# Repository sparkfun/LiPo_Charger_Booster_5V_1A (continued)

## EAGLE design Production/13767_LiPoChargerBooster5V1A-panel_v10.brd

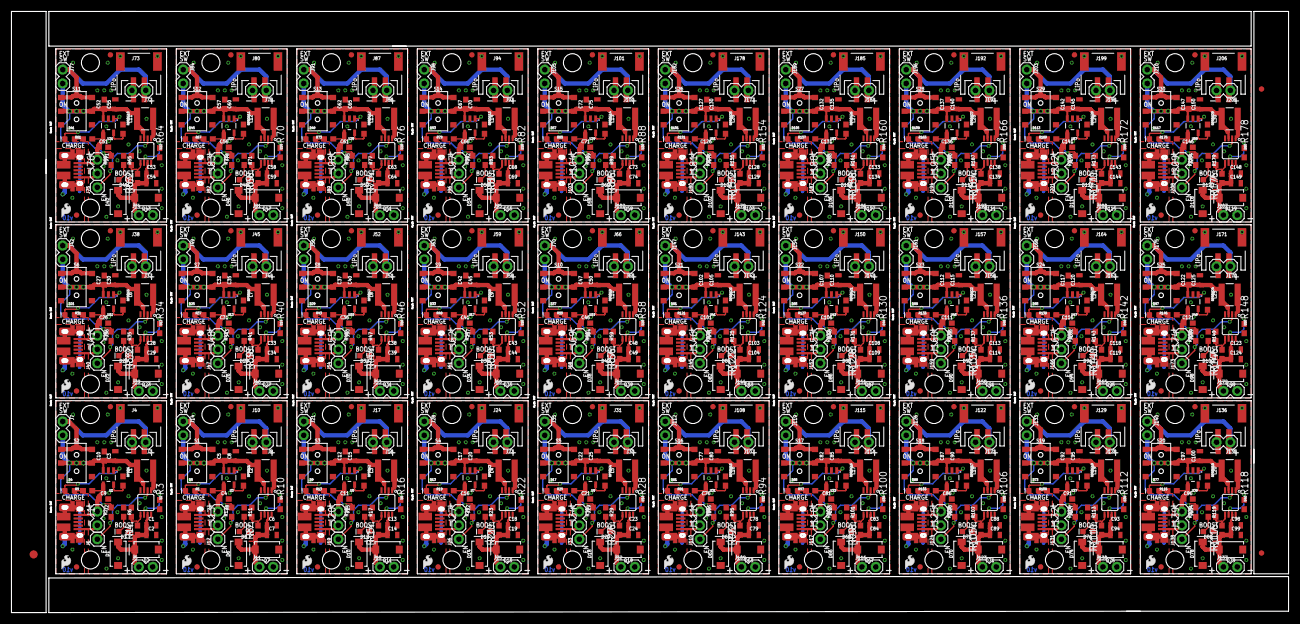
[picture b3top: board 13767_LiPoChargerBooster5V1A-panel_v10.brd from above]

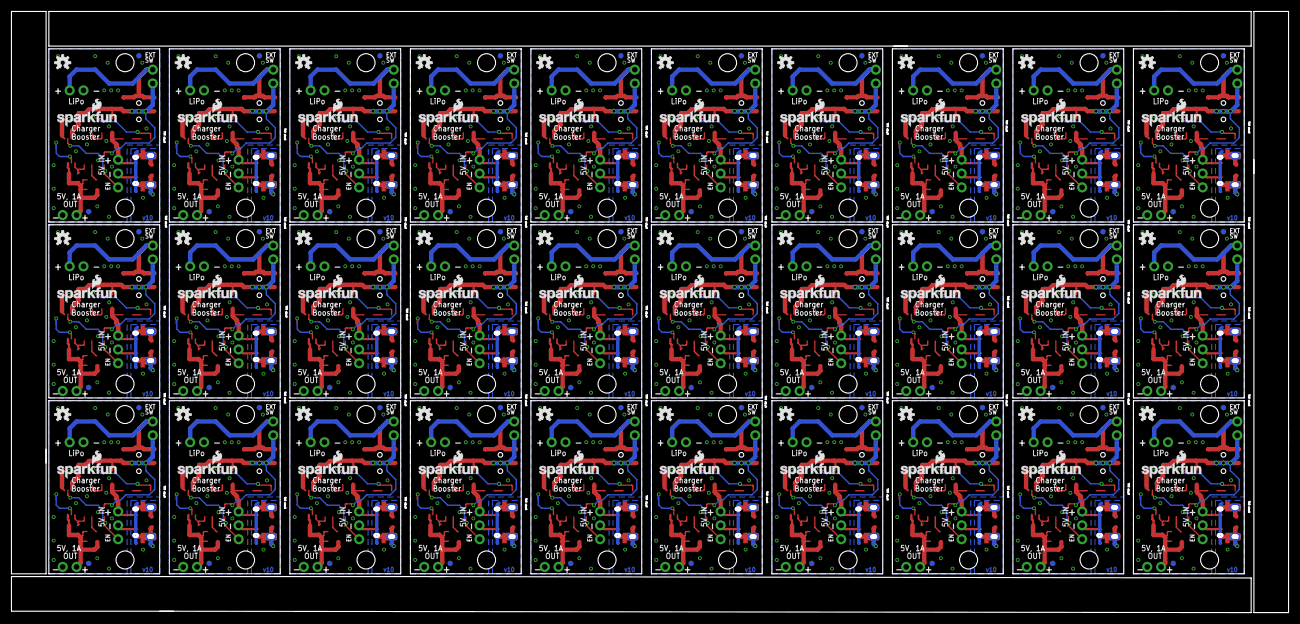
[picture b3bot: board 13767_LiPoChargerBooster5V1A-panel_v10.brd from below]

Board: 2 copper layers, 234.2 x 110.2 mm, 1113 parts (150 on the bottom side), 420 nets.

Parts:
C1, C2, C3, C6, C7, C8, C13, C14, C15, C18, C19, C20, C23, C24, C25, C28, C29, C30, C33, C34, C35, C38, C39, C40, C43, C44, C45, C48, C49, C50, C53, C54, C55, C58, C59, C60, C63, C64, C65, C68, C69, C70, C73, C74, C75, C78, C79, C80, C83, C84, C85, C88, C89, C90, C93, C94, C95, C98, C99, C100, C103, C104, C105, C108, C109, C110, C113, C114, C115, C118, C119, C120, C123, C124, C125, C128, C129, C130, C133, C134, C135, C138, C139, C140, C143, C144, C145, C148, C149, C150: 22uF; 0805
C4, C5, C9, C10, C11, C12, C16, C17, C21, C22, C26, C27, C31, C32, C36, C37, C41, C42, C46, C47, C51, C52, C56, C57, C61, C62, C66, C67, C71, C72, C76, C77, C81, C82, C86, C87, C91, C92, C96, C97, C101, C102, C106, C107, C111, C112, C116, C117, C121, C122, C126, C127, C131, C132, C136, C137, C141, C142, C146, C147: 4.7uF; 0603
D1, D2, D6, D7, D10, D11, D14, D15, D18, D19, D22, D23, D26, D27, D30, D31, D34, D35, D38, D39, D42, D43, D46, D47, D50, D51, D54, D55, D58, D59, D62, D63, D66, D67, D70, D71, D74, D75, D78, D79, D82, D83, D86, D87, D90, D91, D94, D95, D98, D99, D102, D103, D106, D107, D110, D111, D114, D115, D118, D119: 3A/40V/500mV; SMA-DIODE
D3, D8, D12, D16, D20, D24, D28, D32, D36, D40, D44, D48, D52, D56, D60, D64, D68, D72, D76, D80, D84, D88, D92, D96, D100, D104, D108, D112, D116, D120: RED; LED-0603
D4, D5, D9, D13, D17, D21, D25, D29, D33, D37, D41, D45, D49, D53, D57, D61, D65, D69, D73, D77, D81, D85, D89, D93, D97, D101, D105, D109, D113, D117: BLUE; LED-0603
E$1: FIDUCIAL-1.5X3
E$5, E$6: FIDUCIAL-1X2
J1, J13, J20, J27, J34, J41, J48, J55, J62, J69, J76, J83, J90, J97, J104, J111, J118, J125, J132, J139, J146, J153, J160, J167, J174, J181, J188, J195, J202, J209: AMP FCI 10103594-0001LF; USB-MICROB-PTH
J2, J3, J7, J8, J9, J14, J15, J16, J21, J22, J23, J28, J29, J30, J35, J36, J37, J42, J43, J44, J49, J50, J51, J56, J57, J58, J63, J64, J65, J70, J71, J72, J77, J78, J79, J84, J85, J86, J91, J92, J93, J98, J99, J100, J105, J106, J107, J112, J113, J114, J119, J120, J121, J126, J127, J128, J133, J134, J135, J140, J141, J142, J147, J148, J149, J154, J155, J156, J161, J162, J163, J168, J169, J170, J175, J176, J177, J182, J183, J184, J189, J190, J191, J196, J197, J198, J203, J204, J205, J210: PTH; 1X02
J4, J10, J17, J24, J31, J38, J45, J52, J59, J66, J73, J80, J87, J94, J101, J108, J115, J122, J129, J136, J143, J150, J157, J164, J171, J178, J185, J192, J199, J206: JST; JST-2-SMD
J5, J11, J18, J25, J32, J39, J46, J53, J60, J67, J74, J81, J88, J95, J102, J109, J116, J123, J130, J137, J144, J151, J158, J165, J172, J179, J186, J193, J200, J207: 1X02
J6, J12, J19, J26, J33, J40, J47, J54, J61, J68, J75, J82, J89, J96, J103, J110, J117, J124, J131, J138, J145, J152, J159, J166, J173, J180, J187, J194, J201, J208: 1X01
JP1, JP2, JP4, JP10, JP11, JP12, JP13, JP16, JP18, JP19, JP20, JP21, JP25, JP26, JP27, JP28, JP32, JP33, JP34, JP35, JP39, JP40, JP41, JP42, JP46, JP47, JP48, JP49, JP53, JP54, JP55, JP56, JP60, JP61, JP62, JP63, JP67, JP68, JP69, JP70, JP74, JP75, JP76, JP77, JP81, JP82, JP83, JP84, JP88, JP89, JP90, JP91, JP95, JP96, JP97, JP98, JP102, JP103, JP104, JP105, JP109, JP110, JP111, JP112, JP116, JP117, JP118, JP119, JP123, JP124, JP125, JP126, JP130, JP131, JP132, JP133, JP137, JP138, JP139, JP140, JP144, JP145, JP146, JP147, JP151, JP152, JP153, JP154, JP158, JP159, JP160, JP161, JP165, JP166, JP167, JP168, JP172, JP173, JP174, JP175, JP179, JP180, JP181, JP182, JP186, JP187, JP188, JP189, JP193, JP194, JP195, JP196, JP200, JP201, JP202, JP203, JP207, JP208, JP209, JP210: FIDUCIAL1X2; FIDUCIAL-1X2
JP3, JP5, JP14, JP22, JP29, JP36, JP43, JP50, JP57, JP64, JP71, JP78, JP85, JP92, JP99, JP106, JP113, JP120, JP127, JP134, JP141, JP148, JP155, JP162, JP169, JP176, JP183, JP190, JP197, JP204: SFE_LOGO_NAME_FLAME.1_INCH; SFE_LOGO_NAME_FLAME_.1
JP6, JP7, JP8, JP9, JP15, JP17, JP23, JP24, JP30, JP31, JP37, JP38, JP44, JP45, JP51, JP52, JP58, JP59, JP65, JP66, JP72, JP73, JP79, JP80, JP86, JP87, JP93, JP94, JP100, JP101, JP107, JP108, JP114, JP115, JP121, JP122, JP128, JP129, JP135, JP136, JP142, JP143, JP149, JP150, JP156, JP157, JP163, JP164, JP170, JP171, JP177, JP178, JP184, JP185, JP191, JP192, JP198, JP199, JP205, JP206: STAND-OFF
L1, L2, L3, L4, L5, L6, L7, L8, L9, L10, L11, L12, L13, L14, L15, L16, L17, L18, L19, L20, L21, L22, L23, L24, L25, L26, L27, L28, L29, L30: 2.2UH3A; INDUCTOR_4X4MM
LOGO1, LOGO2, LOGO3, LOGO4, LOGO5, LOGO6, LOGO7, LOGO8, LOGO9, LOGO10, LOGO11, LOGO12, LOGO13, LOGO14, LOGO15, LOGO16, LOGO17, LOGO18, LOGO19, LOGO20, LOGO21, LOGO22, LOGO23, LOGO24, LOGO25, LOGO26, LOGO27, LOGO28, LOGO29, LOGO30: SFE_LOGO_FLAME.1_INCH; SFE_LOGO_FLAME_.1
R1, R8, R15, R21, R27, R33, R39, R45, R51, R57, R63, R69, R75, R81, R87, R93, R99, R105, R111, R117, R123, R129, R135, R141, R147, R153, R159, R165, R171, R177: 100k; 0603
R2, R12, R18, R24, R30, R36, R42, R48, R54, R60, R66, R72, R78, R84, R90, R96, R102, R108, R114, R120, R126, R132, R138, R144, R150, R156, R162, R168, R174, R180: 10k; 0603
R3, R10, R16, R22, R28, R34, R40, R46, R52, R58, R64, R70, R76, R82, R88, R94, R100, R106, R112, R118, R124, R130, R136, R142, R148, R154, R160, R166, R172, R178: DNP; 0603
R4, R7, R14, R20, R26, R32, R38, R44, R50, R56, R62, R68, R74, R80, R86, R92, R98, R104, R110, R116, R122, R128, R134, R140, R146, R152, R158, R164, R170, R176: 750K; 0603
R5, R9, R13, R19, R25, R31, R37, R43, R49, R55, R61, R67, R73, R79, R85, R91, R97, R103, R109, R115, R121, R127, R133, R139, R145, R151, R157, R163, R169, R175: 1k; 0603
R6, R11, R17, R23, R29, R35, R41, R47, R53, R59, R65, R71, R77, R83, R89, R95, R101, R107, R113, R119, R125, R131, R137, R143, R149, R155, R161, R167, R173, R179: 4.7k; 0603
RPROG, RPROG1, RPROG2, RPROG3, RPROG4, RPROG5, RPROG6, RPROG7, RPROG8, RPROG9, RPROG10, RPROG11, RPROG12, RPROG13, RPROG14, RPROG15, RPROG16, RPROG17, RPROG18, RPROG19, RPROG20, RPROG21, RPROG22, RPROG23, RPROG24, RPROG25, RPROG26, RPROG27, RPROG28, RPROG29: 2.0k; 0603
S1, S2, S3, S4, S5, S6, S7, S8, S9, S10, S11, S12, S13, S14, S15, S16, S17, S18, S19, S20, S21, S22, S23, S24, S25, S26, S27, S28, S29, S30: SWITCH_DPDT_SMD_AYZ0202
TP1, TP2, TP3, TP4, TP5, TP6, TP7, TP8, TP9, TP10, TP11, TP12, TP13, TP14, TP15, TP16, TP17, TP18, TP19, TP20, TP21, TP22, TP23, TP24, TP25, TP26, TP27, TP28, TP29, TP30: TEST-POINT3; PAD.03X.03
U1, U3, U5, U7, U9, U11, U13, U15, U17, U19, U21, U23, U25, U27, U29, U31, U33, U35, U37, U39, U41, U43, U45, U47, U49, U51, U53, U55, U57, U59: MCP73831; SOT23-5
U2, U4, U6, U8, U10, U12, U14, U16, U18, U20, U22, U24, U26, U28, U30, U32, U34, U36, U38, U40, U42, U44, U46, U48, U50, U52, U54, U56, U58, U60: PAM2401; MSOP8
U$1, U$2, U$3, U$4, U$5, U$6, U$7, U$8, U$9, U$10, U$11, U$12, U$13, U$14, U$15, U$16, U$17, U$18, U$19, U$20, U$21, U$22, U$23, U$24, U$25, U$26, U$27, U$28, U$29, U$30: OSHW-LOGOS; OSHW-LOGO-S

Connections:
5VIN: C9.1, J1.VBUS, J2.1, R9.2, U1.4
5VIN1: C4.1, J8.1, J13.VBUS, R5.2, U3.4
5VIN2: C11.1, J15.1, J20.VBUS, R13.2, U5.4
5VIN3: C16.1, J22.1, J27.VBUS, R19.2, U7.4
5VIN4: C21.1, J29.1, J34.VBUS, R25.2, U9.4
5VIN5: C26.1, J36.1, J41.VBUS, R31.2, U11.4
5VIN6: C31.1, J43.1, J48.VBUS, R37.2, U13.4
5VIN7: C36.1, J50.1, J55.VBUS, R43.2, U15.4
5VIN8: C41.1, J57.1, J62.VBUS, R49.2, U17.4
5VIN9: C46.1, J64.1, J69.VBUS, R55.2, U19.4
5VIN10: C51.1, J71.1, J76.VBUS, R61.2, U21.4
5VIN11: C56.1, J78.1, J83.VBUS, R67.2, U23.4
5VIN12: C61.1, J85.1, J90.VBUS, R73.2, U25.4
5VIN13: C66.1, J92.1, J97.VBUS, R79.2, U27.4
5VIN14: C71.1, J99.1, J104.VBUS, R85.2, U29.4
5VIN15: C76.1, J106.1, J111.VBUS, R91.2, U31.4
5VIN16: C81.1, J113.1, J118.VBUS, R97.2, U33.4
5VIN17: C86.1, J120.1, J125.VBUS, R103.2, U35.4
5VIN18: C91.1, J127.1, J132.VBUS, R109.2, U37.4
5VIN19: C96.1, J134.1, J139.VBUS, R115.2, U39.4
5VIN20: C101.1, J141.1, J146.VBUS, R121.2, U41.4
5VIN21: C106.1, J148.1, J153.VBUS, R127.2, U43.4
5VIN22: C111.1, J155.1, J160.VBUS, R133.2, U45.4
5VIN23: C116.1, J162.1, J167.VBUS, R139.2, U47.4
5VIN24: C121.1, J169.1, J174.VBUS, R145.2, U49.4
5VIN25: C126.1, J176.1, J181.VBUS, R151.2, U51.4
5VIN26: C131.1, J183.1, J188.VBUS, R157.2, U53.4
5VIN27: C136.1, J190.1, J195.VBUS, R163.2, U55.4
5VIN28: C141.1, J197.1, J202.VBUS, R169.2, U57.4
5VIN29: C146.1, J204.1, J209.VBUS, R175.2, U59.4
EN: J6.1, R2.1, U2.2
EN1: J12.1, R12.1, U4.2
EN2: J19.1, R18.1, U6.2
EN3: J26.1, R24.1, U8.2
EN4: J33.1, R30.1, U10.2
EN5: J40.1, R36.1, U12.2
EN6: J47.1, R42.1, U14.2
EN7: J54.1, R48.1, U16.2
EN8: J61.1, R54.1, U18.2
EN9: J68.1, R60.1, U20.2
EN10: J75.1, R66.1, U22.2
EN11: J82.1, R72.1, U24.2
EN12: J89.1, R78.1, U26.2
EN13: J96.1, R84.1, U28.2
EN14: J103.1, R90.1, U30.2
EN15: J110.1, R96.1, U32.2
EN16: J117.1, R102.1, U34.2
EN17: J124.1, R108.1, U36.2
EN18: J131.1, R114.1, U38.2
EN19: J138.1, R120.1, U40.2
EN20: J145.1, R126.1, U42.2
EN21: J152.1, R132.1, U44.2
EN22: J159.1, R138.1, U46.2
EN23: J166.1, R144.1, U48.2
EN24: J173.1, R150.1, U50.2
EN25: J180.1, R156.1, U52.2
EN26: J187.1, R162.1, U54.2
EN27: J194.1, R168.1, U56.2
EN28: J201.1, R174.1, U58.2
EN29: J208.1, R180.1, U60.2
GND: C1.2, C2.2, C3.2, C9.2, C10.2, D1.A, D2.A, J1.GND, J2.2, J3.2, J4.1, J5.2, R1.1, R3.1, R6.1, RPROG.2, U1.2, U2.4, U2.8
GND1: C4.2, C5.2, C6.2, C7.2, C8.2, D6.A, D7.A, J8.2, J9.2, J10.1, J11.2, J13.GND, R8.1, R10.1, R11.1, RPROG1.2, U3.2, U4.4, U4.8
GND2: C11.2, C12.2, C13.2, C14.2, C15.2, D10.A, D11.A, J15.2, J16.2, J17.1, J18.2, J20.GND, R15.1, R16.1, R17.1, RPROG2.2, U5.2, U6.4, U6.8
GND3: C16.2, C17.2, C18.2, C19.2, C20.2, D14.A, D15.A, J22.2, J23.2, J24.1, J25.2, J27.GND, R21.1, R22.1, R23.1, RPROG3.2, U7.2, U8.4, U8.8
GND4: C21.2, C22.2, C23.2, C24.2, C25.2, D18.A, D19.A, J29.2, J30.2, J31.1, J32.2, J34.GND, R27.1, R28.1, R29.1, RPROG4.2, U9.2, U10.4, U10.8
GND5: C26.2, C27.2, C28.2, C29.2, C30.2, D22.A, D23.A, J36.2, J37.2, J38.1, J39.2, J41.GND, R33.1, R34.1, R35.1, RPROG5.2, U11.2, U12.4, U12.8
GND6: C31.2, C32.2, C33.2, C34.2, C35.2, D26.A, D27.A, J43.2, J44.2, J45.1, J46.2, J48.GND, R39.1, R40.1, R41.1, RPROG6.2, U13.2, U14.4, U14.8
GND7: C36.2, C37.2, C38.2, C39.2, C40.2, D30.A, D31.A, J50.2, J51.2, J52.1, J53.2, J55.GND, R45.1, R46.1, R47.1, RPROG7.2, U15.2, U16.4, U16.8
GND8: C41.2, C42.2, C43.2, C44.2, C45.2, D34.A, D35.A, J57.2, J58.2, J59.1, J60.2, J62.GND, R51.1, R52.1, R53.1, RPROG8.2, U17.2, U18.4, U18.8
GND9: C46.2, C47.2, C48.2, C49.2, C50.2, D38.A, D39.A, J64.2, J65.2, J66.1, J67.2, J69.GND, R57.1, R58.1, R59.1, RPROG9.2, U19.2, U20.4, U20.8
GND10: C51.2, C52.2, C53.2, C54.2, C55.2, D42.A, D43.A, J71.2, J72.2, J73.1, J74.2, J76.GND, R63.1, R64.1, R65.1, RPROG10.2, U21.2, U22.4, U22.8
GND11: C56.2, C57.2, C58.2, C59.2, C60.2, D46.A, D47.A, J78.2, J79.2, J80.1, J81.2, J83.GND, R69.1, R70.1, R71.1, RPROG11.2, U23.2, U24.4, U24.8
GND12: C61.2, C62.2, C63.2, C64.2, C65.2, D50.A, D51.A, J85.2, J86.2, J87.1, J88.2, J90.GND, R75.1, R76.1, R77.1, RPROG12.2, U25.2, U26.4, U26.8
GND13: C66.2, C67.2, C68.2, C69.2, C70.2, D54.A, D55.A, J92.2, J93.2, J94.1, J95.2, J97.GND, R81.1, R82.1, R83.1, RPROG13.2, U27.2, U28.4, U28.8
GND14: C71.2, C72.2, C73.2, C74.2, C75.2, D58.A, D59.A, J99.2, J100.2, J101.1, J102.2, J104.GND, R87.1, R88.1, R89.1, RPROG14.2, U29.2, U30.4, U30.8
GND15: C76.2, C77.2, C78.2, C79.2, C80.2, D62.A, D63.A, J106.2, J107.2, J108.1, J109.2, J111.GND, R93.1, R94.1, R95.1, RPROG15.2, U31.2, U32.4, U32.8
GND16: C81.2, C82.2, C83.2, C84.2, C85.2, D66.A, D67.A, J113.2, J114.2, J115.1, J116.2, J118.GND, R99.1, R100.1, R101.1, RPROG16.2, U33.2, U34.4, U34.8
GND17: C86.2, C87.2, C88.2, C89.2, C90.2, D70.A, D71.A, J120.2, J121.2, J122.1, J123.2, J125.GND, R105.1, R106.1, R107.1, RPROG17.2, U35.2, U36.4, U36.8
GND18: C91.2, C92.2, C93.2, C94.2, C95.2, D74.A, D75.A, J127.2, J128.2, J129.1, J130.2, J132.GND, R111.1, R112.1, R113.1, RPROG18.2, U37.2, U38.4, U38.8
GND19: C96.2, C97.2, C98.2, C99.2, C100.2, D78.A, D79.A, J134.2, J135.2, J136.1, J137.2, J139.GND, R117.1, R118.1, R119.1, RPROG19.2, U39.2, U40.4, U40.8
GND20: C101.2, C102.2, C103.2, C104.2, C105.2, D82.A, D83.A, J141.2, J142.2, J143.1, J144.2, J146.GND, R123.1, R124.1, R125.1, RPROG20.2, U41.2, U42.4, U42.8
GND21: C106.2, C107.2, C108.2, C109.2, C110.2, D86.A, D87.A, J148.2, J149.2, J150.1, J151.2, J153.GND, R129.1, R130.1, R131.1, RPROG21.2, U43.2, U44.4, U44.8
GND22: C111.2, C112.2, C113.2, C114.2, C115.2, D90.A, D91.A, J155.2, J156.2, J157.1, J158.2, J160.GND, R135.1, R136.1, R137.1, RPROG22.2, U45.2, U46.4, U46.8
GND23: C116.2, C117.2, C118.2, C119.2, C120.2, D94.A, D95.A, J162.2, J163.2, J164.1, J165.2, J167.GND, R141.1, R142.1, R143.1, RPROG23.2, U47.2, U48.4, U48.8
GND24: C121.2, C122.2, C123.2, C124.2, C125.2, D98.A, D99.A, J169.2, J170.2, J171.1, J172.2, J174.GND, R147.1, R148.1, R149.1, RPROG24.2, U49.2, U50.4, U50.8
GND25: C126.2, C127.2, C128.2, C129.2, C130.2, D102.A, D103.A, J176.2, J177.2, J178.1, J179.2, J181.GND, R153.1, R154.1, R155.1, RPROG25.2, U51.2, U52.4, U52.8
GND26: C131.2, C132.2, C133.2, C134.2, C135.2, D106.A, D107.A, J183.2, J184.2, J185.1, J186.2, J188.GND, R159.1, R160.1, R161.1, RPROG26.2, U53.2, U54.4, U54.8
GND27: C136.2, C137.2, C138.2, C139.2, C140.2, D110.A, D111.A, J190.2, J191.2, J192.1, J193.2, J195.GND, R165.1, R166.1, R167.1, RPROG27.2, U55.2, U56.4, U56.8
GND28: C141.2, C142.2, C143.2, C144.2, C145.2, D114.A, D115.A, J197.2, J198.2, J199.1, J200.2, J202.GND, R171.1, R172.1, R173.1, RPROG28.2, U57.2, U58.4, U58.8
GND29: C146.2, C147.2, C148.2, C149.2, C150.2, D118.A, D119.A, J204.2, J205.2, J206.1, J207.2, J209.GND, R177.1, R178.1, R179.1, RPROG29.2, U59.2, U60.4, U60.8
unnamed: RPROG1.1, U3.5
unnamed: D3.C, R6.2
unnamed: D4.A, R9.1
unnamed: L1.P$2, U2.1
unnamed: R3.2, U2.6
unnamed: D5.C, TP2.P$1, U3.1
unnamed: J3.1, J4.2, J7.1, S2.1, S2.4
unnamed: L2.P$2, U4.1
unnamed: RPROG.1, U1.5
unnamed: R1.2, R4.1, U2.5
unnamed: R7.1, R8.2, U4.5
unnamed: D4.C, TP1.P$1, U1.1
unnamed: R10.2, U4.6
unnamed: J9.1, J10.2, J14.1, S1.1, S1.4
unnamed: D8.C, R11.2
unnamed: D5.A, R5.1
unnamed: RPROG2.1, U5.5
unnamed: D9.C, TP3.P$1, U5.1
unnamed: L3.P$2, U6.1
unnamed: R14.1, R15.2, U6.5
unnamed: R16.2, U6.6
unnamed: J16.1, J17.2, J21.1, S3.1, S3.4
unnamed: D12.C, R17.2
unnamed: D9.A, R13.1
unnamed: RPROG3.1, U7.5
unnamed: D13.C, TP4.P$1, U7.1
unnamed: L4.P$2, U8.1
unnamed: R20.1, R21.2, U8.5
unnamed: R22.2, U8.6
unnamed: J23.1, J24.2, J28.1, S4.1, S4.4
unnamed: D16.C, R23.2
unnamed: D13.A, R19.1
unnamed: RPROG4.1, U9.5
unnamed: D17.C, TP5.P$1, U9.1
unnamed: L5.P$2, U10.1
unnamed: R26.1, R27.2, U10.5
unnamed: R28.2, U10.6
unnamed: J30.1, J31.2, J35.1, S5.1, S5.4
unnamed: D20.C, R29.2
unnamed: D17.A, R25.1
unnamed: RPROG5.1, U11.5
unnamed: D21.C, TP6.P$1, U11.1
unnamed: L6.P$2, U12.1
unnamed: R32.1, R33.2, U12.5
unnamed: R34.2, U12.6
unnamed: J37.1, J38.2, J42.1, S6.1, S6.4
unnamed: D24.C, R35.2
unnamed: D21.A, R31.1
unnamed: RPROG6.1, U13.5
unnamed: D25.C, TP7.P$1, U13.1
unnamed: L7.P$2, U14.1
unnamed: R38.1, R39.2, U14.5
unnamed: R40.2, U14.6
unnamed: J44.1, J45.2, J49.1, S7.1, S7.4
unnamed: D28.C, R41.2
unnamed: D25.A, R37.1
unnamed: RPROG7.1, U15.5
unnamed: D29.C, TP8.P$1, U15.1
unnamed: L8.P$2, U16.1
unnamed: R44.1, R45.2, U16.5
unnamed: R46.2, U16.6
unnamed: J51.1, J52.2, J56.1, S8.1, S8.4
unnamed: D32.C, R47.2
unnamed: D29.A, R43.1
unnamed: RPROG8.1, U17.5
unnamed: D33.C, TP9.P$1, U17.1
unnamed: L9.P$2, U18.1
unnamed: R50.1, R51.2, U18.5
unnamed: R52.2, U18.6
unnamed: J58.1, J59.2, J63.1, S9.1, S9.4
unnamed: D36.C, R53.2
unnamed: D33.A, R49.1
unnamed: RPROG9.1, U19.5
unnamed: D37.C, TP10.P$1, U19.1
unnamed: L10.P$2, U20.1
unnamed: R56.1, R57.2, U20.5
unnamed: R58.2, U20.6
unnamed: J65.1, J66.2, J70.1, S10.1, S10.4
unnamed: D40.C, R59.2
unnamed: D37.A, R55.1
unnamed: RPROG10.1, U21.5
unnamed: D41.C, TP11.P$1, U21.1
unnamed: L11.P$2, U22.1
unnamed: R62.1, R63.2, U22.5
unnamed: R64.2, U22.6
unnamed: J72.1, J73.2, J77.1, S11.1, S11.4
unnamed: D44.C, R65.2
unnamed: D41.A, R61.1
unnamed: RPROG11.1, U23.5
unnamed: D45.C, TP12.P$1, U23.1
unnamed: L12.P$2, U24.1
unnamed: R68.1, R69.2, U24.5
unnamed: R70.2, U24.6
unnamed: J79.1, J80.2, J84.1, S12.1, S12.4
unnamed: D48.C, R71.2
unnamed: D45.A, R67.1
unnamed: RPROG12.1, U25.5
unnamed: D49.C, TP13.P$1, U25.1
unnamed: L13.P$2, U26.1
unnamed: R74.1, R75.2, U26.5
unnamed: R76.2, U26.6
unnamed: J86.1, J87.2, J91.1, S13.1, S13.4
unnamed: D52.C, R77.2
unnamed: D49.A, R73.1
unnamed: RPROG13.1, U27.5
unnamed: D53.C, TP14.P$1, U27.1
unnamed: L14.P$2, U28.1
unnamed: R80.1, R81.2, U28.5
unnamed: R82.2, U28.6
unnamed: J93.1, J94.2, J98.1, S14.1, S14.4
unnamed: D56.C, R83.2
unnamed: D53.A, R79.1
unnamed: RPROG14.1, U29.5
unnamed: D57.C, TP15.P$1, U29.1
unnamed: L15.P$2, U30.1
unnamed: R86.1, R87.2, U30.5
unnamed: R88.2, U30.6
unnamed: J100.1, J101.2, J105.1, S15.1, S15.4
unnamed: D60.C, R89.2
unnamed: D57.A, R85.1
unnamed: RPROG15.1, U31.5
unnamed: D61.C, TP16.P$1, U31.1
unnamed: L16.P$2, U32.1
unnamed: R92.1, R93.2, U32.5
unnamed: R94.2, U32.6
unnamed: J107.1, J108.2, J112.1, S16.1, S16.4
unnamed: D64.C, R95.2
unnamed: D61.A, R91.1
unnamed: RPROG16.1, U33.5
unnamed: D65.C, TP17.P$1, U33.1
unnamed: L17.P$2, U34.1
unnamed: R98.1, R99.2, U34.5
unnamed: R100.2, U34.6
unnamed: J114.1, J115.2, J119.1, S17.1, S17.4
unnamed: D68.C, R101.2
unnamed: D65.A, R97.1
unnamed: RPROG17.1, U35.5
unnamed: D69.C, TP18.P$1, U35.1
unnamed: L18.P$2, U36.1
unnamed: R104.1, R105.2, U36.5
unnamed: R106.2, U36.6
unnamed: J121.1, J122.2, J126.1, S18.1, S18.4
unnamed: D72.C, R107.2
unnamed: D69.A, R103.1
unnamed: RPROG18.1, U37.5
unnamed: D73.C, TP19.P$1, U37.1
unnamed: L19.P$2, U38.1
unnamed: R110.1, R111.2, U38.5
unnamed: R112.2, U38.6
unnamed: J128.1, J129.2, J133.1, S19.1, S19.4
unnamed: D76.C, R113.2
unnamed: D73.A, R109.1
unnamed: RPROG19.1, U39.5
unnamed: D77.C, TP20.P$1, U39.1
unnamed: L20.P$2, U40.1
unnamed: R116.1, R117.2, U40.5
unnamed: R118.2, U40.6
unnamed: J135.1, J136.2, J140.1, S20.1, S20.4
unnamed: D80.C, R119.2
unnamed: D77.A, R115.1
unnamed: RPROG20.1, U41.5
unnamed: D81.C, TP21.P$1, U41.1
unnamed: L21.P$2, U42.1
unnamed: R122.1, R123.2, U42.5
unnamed: R124.2, U42.6
unnamed: J142.1, J143.2, J147.1, S21.1, S21.4
unnamed: D84.C, R125.2
unnamed: D81.A, R121.1
unnamed: RPROG21.1, U43.5
unnamed: D85.C, TP22.P$1, U43.1
unnamed: L22.P$2, U44.1
unnamed: R128.1, R129.2, U44.5
unnamed: R130.2, U44.6
unnamed: J149.1, J150.2, J154.1, S22.1, S22.4
unnamed: D88.C, R131.2
unnamed: D85.A, R127.1
unnamed: RPROG22.1, U45.5
unnamed: D89.C, TP23.P$1, U45.1
unnamed: L23.P$2, U46.1
unnamed: R134.1, R135.2, U46.5
unnamed: R136.2, U46.6
unnamed: J156.1, J157.2, J161.1, S23.1, S23.4
unnamed: D92.C, R137.2
unnamed: D89.A, R133.1
unnamed: RPROG23.1, U47.5
unnamed: D93.C, TP24.P$1, U47.1
unnamed: L24.P$2, U48.1
unnamed: R140.1, R141.2, U48.5
unnamed: R142.2, U48.6
unnamed: J163.1, J164.2, J168.1, S24.1, S24.4
unnamed: D96.C, R143.2
unnamed: D93.A, R139.1
unnamed: RPROG24.1, U49.5
unnamed: D97.C, TP25.P$1, U49.1
unnamed: L25.P$2, U50.1
unnamed: R146.1, R147.2, U50.5
unnamed: R148.2, U50.6
unnamed: J170.1, J171.2, J175.1, S25.1, S25.4
unnamed: D100.C, R149.2
unnamed: D97.A, R145.1
unnamed: RPROG25.1, U51.5
unnamed: D101.C, TP26.P$1, U51.1
unnamed: L26.P$2, U52.1
unnamed: R152.1, R153.2, U52.5
unnamed: R154.2, U52.6
unnamed: J177.1, J178.2, J182.1, S26.1, S26.4
unnamed: D104.C, R155.2
unnamed: D101.A, R151.1
unnamed: RPROG26.1, U53.5
unnamed: D105.C, TP27.P$1, U53.1
unnamed: L27.P$2, U54.1
unnamed: R158.1, R159.2, U54.5
unnamed: R160.2, U54.6
unnamed: J184.1, J185.2, J189.1, S27.1, S27.4
unnamed: D108.C, R161.2
unnamed: D105.A, R157.1
unnamed: RPROG27.1, U55.5
unnamed: D109.C, TP28.P$1, U55.1
unnamed: L28.P$2, U56.1
unnamed: R164.1, R165.2, U56.5
unnamed: R166.2, U56.6
unnamed: J191.1, J192.2, J196.1, S28.1, S28.4
unnamed: D112.C, R167.2
unnamed: D109.A, R163.1
unnamed: RPROG28.1, U57.5
unnamed: D113.C, TP29.P$1, U57.1
unnamed: L29.P$2, U58.1
unnamed: R170.1, R171.2, U58.5
unnamed: R172.2, U58.6
unnamed: J198.1, J199.2, J203.1, S29.1, S29.4
unnamed: D116.C, R173.2
unnamed: D113.A, R169.1
unnamed: RPROG29.1, U59.5
unnamed: D117.C, TP30.P$1, U59.1
unnamed: L30.P$2, U60.1
unnamed: R176.1, R177.2, U60.5
unnamed: R178.2, U60.6
unnamed: J205.1, J206.2, J210.1, S30.1, S30.4
unnamed: D120.C, R179.2
unnamed: D117.A, R175.1
SHIELD: J1.P$1, J1.P$2, J1.P$3, J1.P$4, J1.P$6, J1.P$8, J1.P$10, J1.P$12, J1.SHEILD2, J1.SHIELD, J1.SHIELD3, J1.SHIELD4
SHIELD1: J13.P$1, J13.P$2, J13.P$3, J13.P$4, J13.P$6, J13.P$8, J13.P$10, J13.P$12, J13.SHEILD2, J13.SHIELD, J13.SHIELD3, J13.SHIELD4
SHIELD2: J20.P$1, J20.P$2, J20.P$3, J20.P$4, J20.P$6, J20.P$8, J20.P$10, J20.P$12, J20.SHEILD2, J20.SHIELD, J20.SHIELD3, J20.SHIELD4
SHIELD3: J27.P$1, J27.P$2, J27.P$3, J27.P$4, J27.P$6, J27.P$8, J27.P$10, J27.P$12, J27.SHEILD2, J27.SHIELD, J27.SHIELD3, J27.SHIELD4
SHIELD4: J34.P$1, J34.P$2, J34.P$3, J34.P$4, J34.P$6, J34.P$8, J34.P$10, J34.P$12, J34.SHEILD2, J34.SHIELD, J34.SHIELD3, J34.SHIELD4
SHIELD5: J41.P$1, J41.P$2, J41.P$3, J41.P$4, J41.P$6, J41.P$8, J41.P$10, J41.P$12, J41.SHEILD2, J41.SHIELD, J41.SHIELD3, J41.SHIELD4
SHIELD6: J48.P$1, J48.P$2, J48.P$3, J48.P$4, J48.P$6, J48.P$8, J48.P$10, J48.P$12, J48.SHEILD2, J48.SHIELD, J48.SHIELD3, J48.SHIELD4
SHIELD7: J55.P$1, J55.P$2, J55.P$3, J55.P$4, J55.P$6, J55.P$8, J55.P$10, J55.P$12, J55.SHEILD2, J55.SHIELD, J55.SHIELD3, J55.SHIELD4
SHIELD8: J62.P$1, J62.P$2, J62.P$3, J62.P$4, J62.P$6, J62.P$8, J62.P$10, J62.P$12, J62.SHEILD2, J62.SHIELD, J62.SHIELD3, J62.SHIELD4
SHIELD9: J69.P$1, J69.P$2, J69.P$3, J69.P$4, J69.P$6, J69.P$8, J69.P$10, J69.P$12, J69.SHEILD2, J69.SHIELD, J69.SHIELD3, J69.SHIELD4
SHIELD10: J76.P$1, J76.P$2, J76.P$3, J76.P$4, J76.P$6, J76.P$8, J76.P$10, J76.P$12, J76.SHEILD2, J76.SHIELD, J76.SHIELD3, J76.SHIELD4
SHIELD11: J83.P$1, J83.P$2, J83.P$3, J83.P$4, J83.P$6, J83.P$8, J83.P$10, J83.P$12, J83.SHEILD2, J83.SHIELD, J83.SHIELD3, J83.SHIELD4
SHIELD12: J90.P$1, J90.P$2, J90.P$3, J90.P$4, J90.P$6, J90.P$8, J90.P$10, J90.P$12, J90.SHEILD2, J90.SHIELD, J90.SHIELD3, J90.SHIELD4
SHIELD13: J97.P$1, J97.P$2, J97.P$3, J97.P$4, J97.P$6, J97.P$8, J97.P$10, J97.P$12, J97.SHEILD2, J97.SHIELD, J97.SHIELD3, J97.SHIELD4
SHIELD14: J104.P$1, J104.P$2, J104.P$3, J104.P$4, J104.P$6, J104.P$8, J104.P$10, J104.P$12, J104.SHEILD2, J104.SHIELD, J104.SHIELD3, J104.SHIELD4
SHIELD15: J111.P$1, J111.P$2, J111.P$3, J111.P$4, J111.P$6, J111.P$8, J111.P$10, J111.P$12, J111.SHEILD2, J111.SHIELD, J111.SHIELD3, J111.SHIELD4
SHIELD16: J118.P$1, J118.P$2, J118.P$3, J118.P$4, J118.P$6, J118.P$8, J118.P$10, J118.P$12, J118.SHEILD2, J118.SHIELD, J118.SHIELD3, J118.SHIELD4
SHIELD17: J125.P$1, J125.P$2, J125.P$3, J125.P$4, J125.P$6, J125.P$8, J125.P$10, J125.P$12, J125.SHEILD2, J125.SHIELD, J125.SHIELD3, J125.SHIELD4
SHIELD18: J132.P$1, J132.P$2, J132.P$3, J132.P$4, J132.P$6, J132.P$8, J132.P$10, J132.P$12, J132.SHEILD2, J132.SHIELD, J132.SHIELD3, J132.SHIELD4
SHIELD19: J139.P$1, J139.P$2, J139.P$3, J139.P$4, J139.P$6, J139.P$8, J139.P$10, J139.P$12, J139.SHEILD2, J139.SHIELD, J139.SHIELD3, J139.SHIELD4
SHIELD20: J146.P$1, J146.P$2, J146.P$3, J146.P$4, J146.P$6, J146.P$8, J146.P$10, J146.P$12, J146.SHEILD2, J146.SHIELD, J146.SHIELD3, J146.SHIELD4
SHIELD21: J153.P$1, J153.P$2, J153.P$3, J153.P$4, J153.P$6, J153.P$8, J153.P$10, J153.P$12, J153.SHEILD2, J153.SHIELD, J153.SHIELD3, J153.SHIELD4
SHIELD22: J160.P$1, J160.P$2, J160.P$3, J160.P$4, J160.P$6, J160.P$8, J160.P$10, J160.P$12, J160.SHEILD2, J160.SHIELD, J160.SHIELD3, J160.SHIELD4
SHIELD23: J167.P$1, J167.P$2, J167.P$3, J167.P$4, J167.P$6, J167.P$8, J167.P$10, J167.P$12, J167.SHEILD2, J167.SHIELD, J167.SHIELD3, J167.SHIELD4
SHIELD24: J174.P$1, J174.P$2, J174.P$3, J174.P$4, J174.P$6, J174.P$8, J174.P$10, J174.P$12, J174.SHEILD2, J174.SHIELD, J174.SHIELD3, J174.SHIELD4
SHIELD25: J181.P$1, J181.P$2, J181.P$3, J181.P$4, J181.P$6, J181.P$8, J181.P$10, J181.P$12, J181.SHEILD2, J181.SHIELD, J181.SHIELD3, J181.SHIELD4
SHIELD26: J188.P$1, J188.P$2, J188.P$3, J188.P$4, J188.P$6, J188.P$8, J188.P$10, J188.P$12, J188.SHEILD2, J188.SHIELD, J188.SHIELD3, J188.SHIELD4
SHIELD27: J195.P$1, J195.P$2, J195.P$3, J195.P$4, J195.P$6, J195.P$8, J195.P$10, J195.P$12, J195.SHEILD2, J195.SHIELD, J195.SHIELD3, J195.SHIELD4
SHIELD28: J202.P$1, J202.P$2, J202.P$3, J202.P$4, J202.P$6, J202.P$8, J202.P$10, J202.P$12, J202.SHEILD2, J202.SHIELD, J202.SHIELD3, J202.SHIELD4
SHIELD29: J209.P$1, J209.P$2, J209.P$3, J209.P$4, J209.P$6, J209.P$8, J209.P$10, J209.P$12, J209.SHEILD2, J209.SHIELD, J209.SHIELD3, J209.SHIELD4
VBATT: C3.1, C10.1, J7.2, L1.P$1, R2.2, S2.2, S2.5, U1.3, U2.3
VBATT1: C5.1, C8.1, J14.2, L2.P$1, R12.2, S1.2, S1.5, U3.3, U4.3
VBATT2: C12.1, C15.1, J21.2, L3.P$1, R18.2, S3.2, S3.5, U5.3, U6.3
VBATT3: C17.1, C20.1, J28.2, L4.P$1, R24.2, S4.2, S4.5, U7.3, U8.3
VBATT4: C22.1, C25.1, J35.2, L5.P$1, R30.2, S5.2, S5.5, U9.3, U10.3
VBATT5: C27.1, C30.1, J42.2, L6.P$1, R36.2, S6.2, S6.5, U11.3, U12.3
VBATT6: C32.1, C35.1, J49.2, L7.P$1, R42.2, S7.2, S7.5, U13.3, U14.3
VBATT7: C37.1, C40.1, J56.2, L8.P$1, R48.2, S8.2, S8.5, U15.3, U16.3
VBATT8: C42.1, C45.1, J63.2, L9.P$1, R54.2, S9.2, S9.5, U17.3, U18.3
VBATT9: C47.1, C50.1, J70.2, L10.P$1, R60.2, S10.2, S10.5, U19.3, U20.3
VBATT10: C52.1, C55.1, J77.2, L11.P$1, R66.2, S11.2, S11.5, U21.3, U22.3
VBATT11: C57.1, C60.1, J84.2, L12.P$1, R72.2, S12.2, S12.5, U23.3, U24.3
VBATT12: C62.1, C65.1, J91.2, L13.P$1, R78.2, S13.2, S13.5, U25.3, U26.3
VBATT13: C67.1, C70.1, J98.2, L14.P$1, R84.2, S14.2, S14.5, U27.3, U28.3
VBATT14: C72.1, C75.1, J105.2, L15.P$1, R90.2, S15.2, S15.5, U29.3, U30.3
VBATT15: C77.1, C80.1, J112.2, L16.P$1, R96.2, S16.2, S16.5, U31.3, U32.3
VBATT16: C82.1, C85.1, J119.2, L17.P$1, R102.2, S17.2, S17.5, U33.3, U34.3
VBATT17: C87.1, C90.1, J126.2, L18.P$1, R108.2, S18.2, S18.5, U35.3, U36.3
VBATT18: C92.1, C95.1, J133.2, L19.P$1, R114.2, S19.2, S19.5, U37.3, U38.3
VBATT19: C97.1, C100.1, J140.2, L20.P$1, R120.2, S20.2, S20.5, U39.3, U40.3
VBATT20: C102.1, C105.1, J147.2, L21.P$1, R126.2, S21.2, S21.5, U41.3, U42.3
VBATT21: C107.1, C110.1, J154.2, L22.P$1, R132.2, S22.2, S22.5, U43.3, U44.3
VBATT22: C112.1, C115.1, J161.2, L23.P$1, R138.2, S23.2, S23.5, U45.3, U46.3
VBATT23: C117.1, C120.1, J168.2, L24.P$1, R144.2, S24.2, S24.5, U47.3, U48.3
VBATT24: C122.1, C125.1, J175.2, L25.P$1, R150.2, S25.2, S25.5, U49.3, U50.3
VBATT25: C127.1, C130.1, J182.2, L26.P$1, R156.2, S26.2, S26.5, U51.3, U52.3
VBATT26: C132.1, C135.1, J189.2, L27.P$1, R162.2, S27.2, S27.5, U53.3, U54.3
VBATT27: C137.1, C140.1, J196.2, L28.P$1, R168.2, S28.2, S28.5, U55.3, U56.3
VBATT28: C142.1, C145.1, J203.2, L29.P$1, R174.2, S29.2, S29.5, U57.3, U58.3
VBATT29: C147.1, C150.1, J210.2, L30.P$1, R180.2, S30.2, S30.5, U59.3, U60.3
VCC: C1.1, C2.1, D1.C, D2.C, D3.A, J5.1, R4.2, U2.7
VCC1: C6.1, C7.1, D6.C, D7.C, D8.A, J11.1, R7.2, U4.7
VCC2: C13.1, C14.1, D10.C, D11.C, D12.A, J18.1, R14.2, U6.7
VCC3: C18.1, C19.1, D14.C, D15.C, D16.A, J25.1, R20.2, U8.7
VCC4: C23.1, C24.1, D18.C, D19.C, D20.A, J32.1, R26.2, U10.7
VCC5: C28.1, C29.1, D22.C, D23.C, D24.A, J39.1, R32.2, U12.7
VCC6: C33.1, C34.1, D26.C, D27.C, D28.A, J46.1, R38.2, U14.7
VCC7: C38.1, C39.1, D30.C, D31.C, D32.A, J53.1, R44.2, U16.7
VCC8: C43.1, C44.1, D34.C, D35.C, D36.A, J60.1, R50.2, U18.7
VCC9: C48.1, C49.1, D38.C, D39.C, D40.A, J67.1, R56.2, U20.7
VCC10: C53.1, C54.1, D42.C, D43.C, D44.A, J74.1, R62.2, U22.7
VCC11: C58.1, C59.1, D46.C, D47.C, D48.A, J81.1, R68.2, U24.7
VCC12: C63.1, C64.1, D50.C, D51.C, D52.A, J88.1, R74.2, U26.7
VCC13: C68.1, C69.1, D54.C, D55.C, D56.A, J95.1, R80.2, U28.7
VCC14: C73.1, C74.1, D58.C, D59.C, D60.A, J102.1, R86.2, U30.7
VCC15: C78.1, C79.1, D62.C, D63.C, D64.A, J109.1, R92.2, U32.7
VCC16: C83.1, C84.1, D66.C, D67.C, D68.A, J116.1, R98.2, U34.7
VCC17: C88.1, C89.1, D70.C, D71.C, D72.A, J123.1, R104.2, U36.7
VCC18: C93.1, C94.1, D74.C, D75.C, D76.A, J130.1, R110.2, U38.7
VCC19: C98.1, C99.1, D78.C, D79.C, D80.A, J137.1, R116.2, U40.7
VCC20: C103.1, C104.1, D82.C, D83.C, D84.A, J144.1, R122.2, U42.7
VCC21: C108.1, C109.1, D86.C, D87.C, D88.A, J151.1, R128.2, U44.7
VCC22: C113.1, C114.1, D90.C, D91.C, D92.A, J158.1, R134.2, U46.7
VCC23: C118.1, C119.1, D94.C, D95.C, D96.A, J165.1, R140.2, U48.7
VCC24: C123.1, C124.1, D98.C, D99.C, D100.A, J172.1, R146.2, U50.7
VCC25: C128.1, C129.1, D102.C, D103.C, D104.A, J179.1, R152.2, U52.7
VCC26: C133.1, C134.1, D106.C, D107.C, D108.A, J186.1, R158.2, U54.7
VCC27: C138.1, C139.1, D110.C, D111.C, D112.A, J193.1, R164.2, U56.7
VCC28: C143.1, C144.1, D114.C, D115.C, D116.A, J200.1, R170.2, U58.7
VCC29: C148.1, C149.1, D118.C, D119.C, D120.A, J207.1, R176.2, U60.7

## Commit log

2017-05-17 Created possible sparkfun product
2017-07-10 Not sure why this wasn't pushed
2017-07-19 Ready for review
2017-07-19 Added staking vias
2017-07-20 Post reivew changes
2017-07-24 Updated components and checked against the checklist, moved temp parts into normal eagle libs
2017-07-31 Approved dimension DRC violations
2017-08-02 panel
2017-09-21 Changed pull up to 750k, added photos
2017-09-22 Added datasheets
2017-09-29 Finished github documentation and cleaned repo
2017-09-29 Added product name
2017-09-29 Update README.md
    Re-add version history if there is ever a revision with the board.
